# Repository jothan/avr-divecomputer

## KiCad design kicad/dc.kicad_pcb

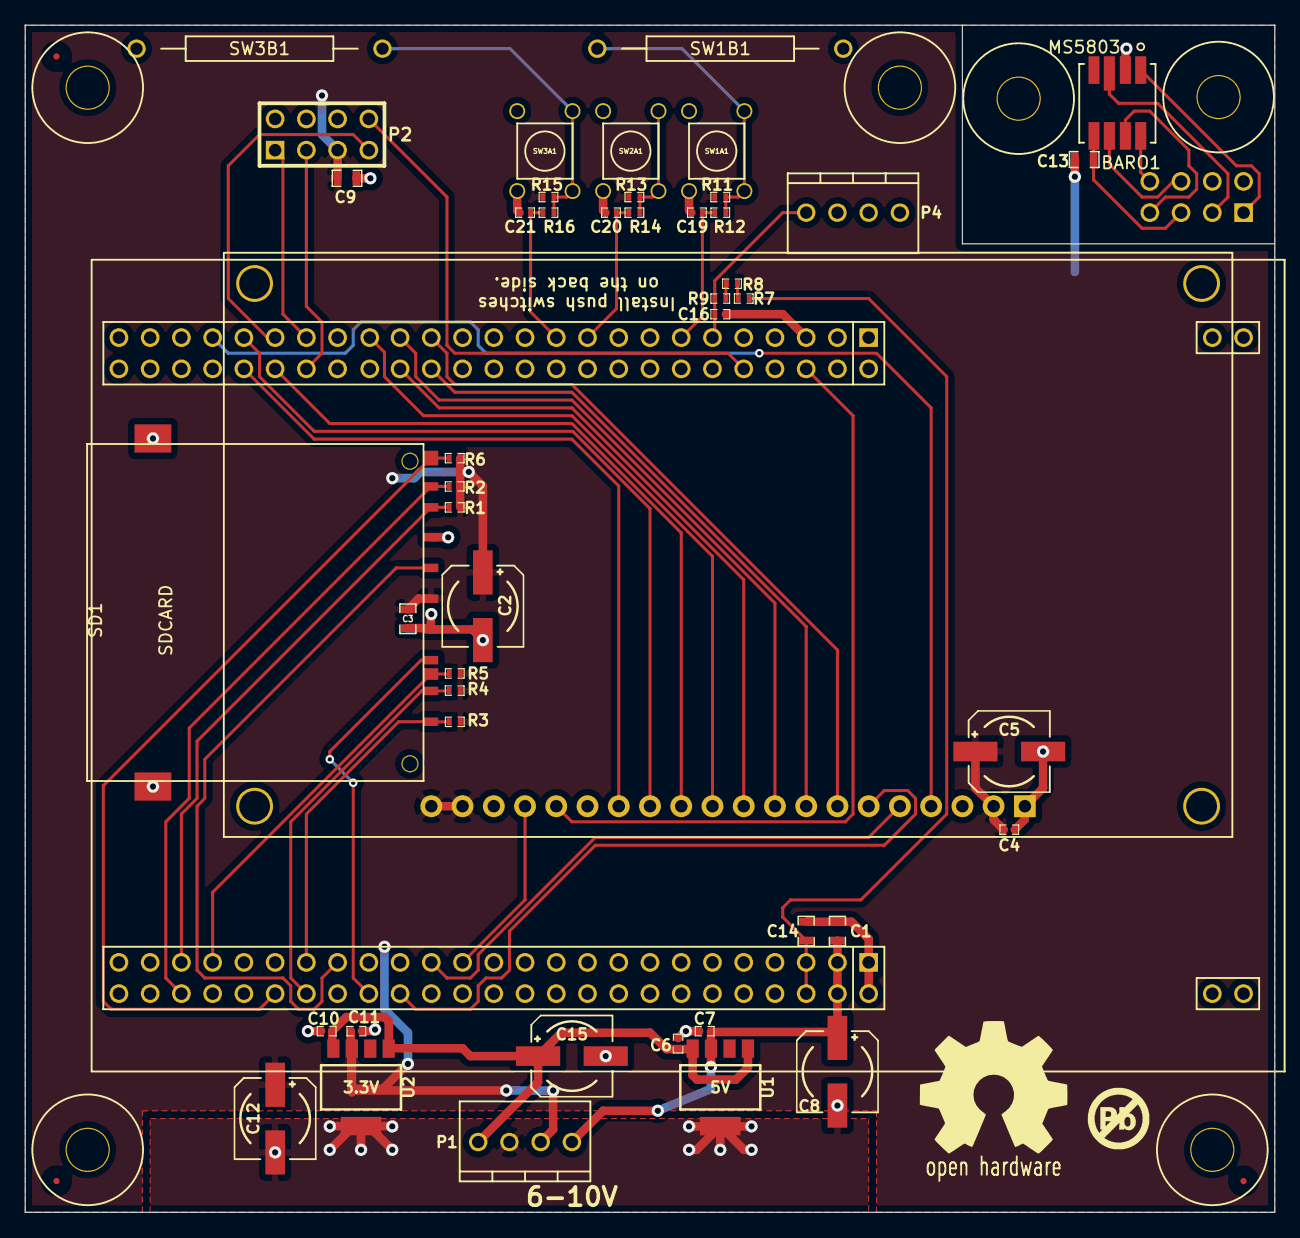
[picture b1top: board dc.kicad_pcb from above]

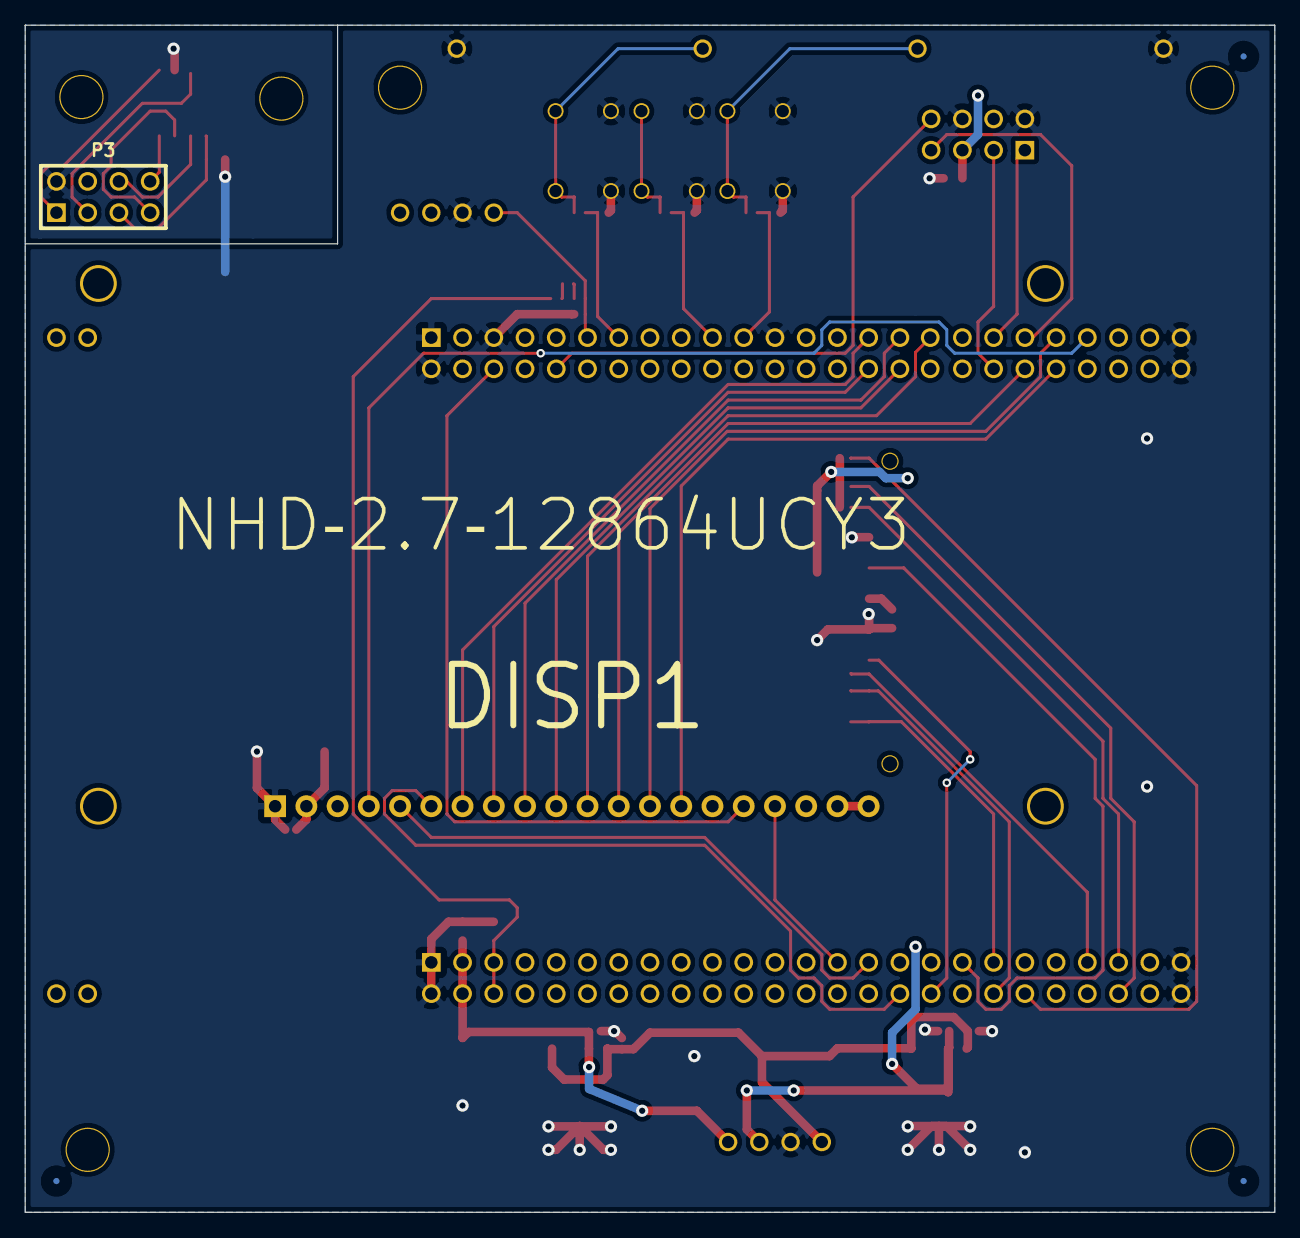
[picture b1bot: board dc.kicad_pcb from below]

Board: 2 copper layers, 101.6 x 96.5 mm, 58 parts (2 on the bottom side), 45 nets.

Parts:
BARO1: MS5803
C1, C3, C9, C13, C14: 10uF; SM0603_Capa
C2, C5, C8, C12, C15: 150uF; c_elec_6.3x5.7
C4, C6, C7, C10, C11, C16, C19, C20, C21: 1uF; SM0402_c
DISP1: NHD‐2.7‐12864UCY3
FID1: FID**; FIDUCIAL
FID2, FID3: VAL**; FIDUCIAL
J1: STM32F4_DISCOVERY_HEADER; stm32f4_discovery_header
M3_MOUNT, M3_MOUNT#2, M3_MOUNT#3, M3_MOUNT#4, M3_MOUNT#5, M3_MOUNT#6: VAL**; M3_MOUNT
P1, P4: CONN_4; ED10563-ND
P2, P3: CONN_4X2; pin_array_4x2
R1, R2, R3, R4, R5, R6, R7, R8, R9, R11, R12, R13, R14, R15, R16: 100k; SM0402
SD1: SDCARD; 101-00405-75-ND
SW1A1, SW2A1, SW3A1: SW_PUSH; P8008S-ND
SW1B1, SW3B1: SW_PUSH; REED
U1: 5V; SOT-223-5
U2: 3.3V; SOT-223-5

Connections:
+3.3V: C2.1, C3.1, C4.1, C5.1, C9.1, C11.1, C12.1, DISP1.2, DISP1.19, DISP1.20, P1.3, P2.5, R1.1, R2.1, R3.1, R4.1, R5.2, R6.2, R11.2, R13.2, R15.2, SD1.4, U2.3
+5V: C1.1, C7.1, C8.1, J1.97, J1.98, P1.4, U1.3
+BATT: C6.1, C10.1, C15.1, P1.1, U1.1, U1.4, U2.1, U2.4
DEPTH_CS: J1.38, P2.3
FSMC_A16: DISP1.4, J1.43
FSMC_D08: DISP1.7, J1.29
FSMC_D09: DISP1.8, J1.30
FSMC_D10: DISP1.9, J1.31
FSMC_D11: DISP1.10, J1.32
FSMC_D12: DISP1.11, J1.33
FSMC_D13: DISP1.12, J1.40
FSMC_D14: DISP1.13, J1.41
FSMC_D15: DISP1.14, J1.42
FSMC_NE1: DISP1.17, J1.73
FSMC_NOE: DISP1.6, J1.70
FSMC_NWE: DISP1.5, J1.71
GND: BARO1.2, C1.2, C2.2, C3.2, C4.2, C5.2, C6.2, C7.2, C8.2, C9.2, C10.2, C11.2, C12.2, C13.2, C14.2, C15.2, C16.2, C19.2, C20.2, C21.2, DISP1.1, J1.1, J1.2, J1.5, J1.23, J1.49, J1.50, J1.51, J1.52, J1.99, J1.100, P1.2, P2.2, P2.6, P3.2, P4.3, SD1.3, SD1.6, SD1.10, SW1A1.1, SW1B1.1, SW2A1.1, SW3A1.1, SW3B1.1, U1.5, U2.5
unnamed: BARO1.1, P3.1
unnamed: BARO1.6, P3.6
unnamed: BARO1.7, P3.7
unnamed: BARO1.8, P3.8
unnamed: R7.1, R8.2
unnamed: R8.1, R9.1
unnamed: BARO1.5, C13.1, P3.5
unnamed: BARO1.3, P3.3
unnamed: R13.1, R14.1, SW2A1.2
unnamed: R15.1, R16.1, SW3A1.2, SW3B1.2
unnamed: R11.1, R12.1, SW1A1.2, SW1B1.2
RESET: DISP1.16, J1.6
SDIO_CK: J1.65, SD1.5
SDIO_CMD: J1.68, SD1.2
SDIO_D0: J1.55, R1.2, SD1.7
SDIO_D1: J1.56, R2.2, SD1.8
SDIO_D2: J1.63, R3.2, SD1.9
SDIO_D3: J1.64, R4.2, SD1.1
SD_CD: J1.57, R5.1, SD1.11
SD_WP: J1.62, R6.1, SD1.12
SPI2_MISO: J1.10, P2.8
SPI2_MOSI: J1.39, P2.7
SPI2_SCK: J1.37, P2.1
STM_3V: C14.1, J1.95, J1.96, R7.2
SW1: C19.1, J1.13, R12.2
SW2: C20.1, J1.19, R14.2
SW3: C21.1, J1.21, R16.2
WATER: C16.1, J1.11, P4.4, R9.2

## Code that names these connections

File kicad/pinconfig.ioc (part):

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Mcu.Name=STM32F407V(E-G)Tx
Mcu.Package=LQFP100
Mcu.UserName=STM32F407VGTx
PA11.Mode=Device_Only
PA11.Signal=USB_OTG_FS_DM
PA12.Mode=Device_Only
PA12.Signal=USB_OTG_FS_DP
PA9.Mode=Activate_VBUS
PA9.Signal=USB_OTG_FS_VBUS
PB12.Signal=GPIO_Output
PB13.Mode=Full_Duplex_Master
PB13.Signal=SPI2_SCK
PB14.Mode=Full_Duplex_Master
PB14.Signal=SPI2_MISO
PB15.Mode=Full_Duplex_Master
PB15.Signal=SPI2_MOSI
PC10.Mode=SD_4_bits_Wide_bus
PC10.Signal=SDIO_D2
PC11.Mode=SD_4_bits_Wide_bus
PC11.Signal=SDIO_D3
PC12.Mode=SD_4_bits_Wide_bus
PC12.Signal=SDIO_CK
PC8.Mode=SD_4_bits_Wide_bus
PC8.Signal=SDIO_D0
PC9.Mode=SD_4_bits_Wide_bus
PC9.Signal=SDIO_D1
PD0.Signal=FSMC_D2_DA2
PD1.Signal=FSMC_D3_DA3
PD11.Signal=FSMC_A16_CLE
PD14.Signal=FSMC_D0_DA0
PD15.Signal=FSMC_D1_DA1
PD2.Mode=SD_4_bits_Wide_bus
PD2.Signal=SDIO_CMD
PD4.Signal=FSMC_NOE
PD5.Signal=FSMC_NWE
PD7.Signal=FSMC_NE1
PE10.Signal=FSMC_D7_DA7
PE7.Signal=FSMC_D4_DA4
PE8.Signal=FSMC_D5_DA5
PE9.Signal=FSMC_D6_DA6
RCC.HSE_VALUE=25000000

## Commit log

2014-08-15 Script setup.
2014-08-22 Some basic SPI bus handling.
2014-10-19 Machin.
2014-10-19 Commit de code qui sera pas utilisé.
2014-10-19 Prototype #1.
2014-10-19 Erreur de numéro de pièce.
2014-10-20 Simplification schéma.
2014-10-20 Correctif des condensateurs, la plupart avait un voltage maximal insuffisant.
2014-10-26 Modifier le projet en mode STM32.
2014-10-26 Download dossier système.
2014-11-04 Gros update. Code de sensor de pression simple.
2014-11-08 Préparation pour DMA.
2014-11-08 Timer simple.
2014-11-09 Flag explicite sur les TimerItem.
2014-11-09 Éviter les effets de bord de schedule.
2014-11-09 Sensor de pression pleinement controllé par interruption et DMA.
    Il reste à nettoyer les états et améliorer la gestion d'erreur.
2014-11-09 Noter le modèle du chip.
2014-11-15 Code de base pour initialiser l'écran.
2014-11-16 Code boboche mais suffisant pour tester les communications avec la carte SD.
2015-01-11 Ajustement.
2015-01-13 Build avec scons. Plus besoin de eclipse pour générer les makefiles.
2015-01-15 Update de la gestion du code externe.
    La distro Micro-OS III est utilisée car celle-ci regroupe tous les
    fichiers de base requis.
2015-01-17 Écran passe 1.
2015-01-17 Setup pour u8glib.
2015-01-25 Activer les floats dans printf.
2015-01-25 Options pour float.
2015-01-26 Add tissus initialization
2015-03-21 Start to use object approch for buhlman model
2015-03-22 Fix error size array initialization
2015-03-22 Nouveau release fatfs.
2015-03-22 Use standard constant name
2015-03-22 Sérializer les tâches qui touchent au device.
    Permet de faire scons -j8 upload run direct.
2015-03-22 Fix build.
2015-03-22 Nettoyage du main, Marc semble avoir déplacé ca dans les fichiers appropriés.
2015-03-22 Ne pas dupliquer les sources avec scons.
    Permet à netbeans de communiquer les bons noms de fichier pour le
    débug. Il se peut que scons aie un comportement inhabituel, restons
    sur nos gardes.
2015-03-22 Mettre les fichiers netbean dans git.
2015-03-22 Fix de calcul de capacité de la carte.
2015-03-22 Afficher la capacité de la carte SD.
2015-03-22 Commande "attach" pour netbeans.
2015-03-23 Use enum class instead of standard enum.
2015-03-24 Add two method to get temperature and pressus in a specific format. Method is empty actually
2015-03-27 Update uos.
2015-03-27 Patch plus requise avec la dernière version du HAL.
2015-03-28 Support FatFS de base.
2015-04-05 Include oublié.
2015-04-05 Ne pas hardcoder 512 bytes.
2015-04-05 API un peu plus sain pour le capteur de pression.
2015-04-05 Blinder depth contre les séquences d'appel invalides.
2015-04-05 Includes manquant.
2015-04-05 Rejiggage des définitions de pins.
2015-04-05 Use Buhlmann C model Use getPressue method from sensor
2015-04-05 FileUtility to read and write an file. Read method put value in a map Write method have a map in parameter.
2015-04-05 enable _USE_STRFUNC
2015-04-05 Set variable to 0
2015-04-05 Add an include
2015-04-05 Rendre plus silencieux les appels de carte SD.
2015-04-06 Rename file, first letter is lowercase.
2015-04-11 Add rtc code
2015-04-11 Improve test rtc code
2015-04-17 Rename depth to pressureSensor Create a class for waterSensor Add methode in configComputer Clean code
2015-06-07 Cleanup du main. SVP éviter les longs délais de startup.
2015-06-07 Classe RTC avec affichage sur l'écran.
    Le code évite de resetter l'horloge si celle-ci est déja initialisée.
2015-06-07 Code des boutons préliminaire.
2015-06-12 Add a class for rtc Add code to calculate ndl, should be improved to be used with trimix.
2015-07-11 Merge origin/master
    Conflicts:
    src/_initialize_hardware.c
    src/main.cpp
2015-08-01 Ne pas mettre les fichiers exécutables inutilement.
2015-08-01 Nouvelle version de KiCad.
2015-08-02 Continuation du transfert.
